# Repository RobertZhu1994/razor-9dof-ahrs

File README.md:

Razor AHRS v1.4.2
---

This is a "fab-able" version of the <a href="https://www.sparkfun.com/products/retired/10736">Sparkfun 9DOF IMU board</a>, modified so that it can be made with a desktop CNC router.

Full documentation on <a href="https://www.instructables.com/id/9-Degrees-of-Freedom-IMU/">Instructables</a>.

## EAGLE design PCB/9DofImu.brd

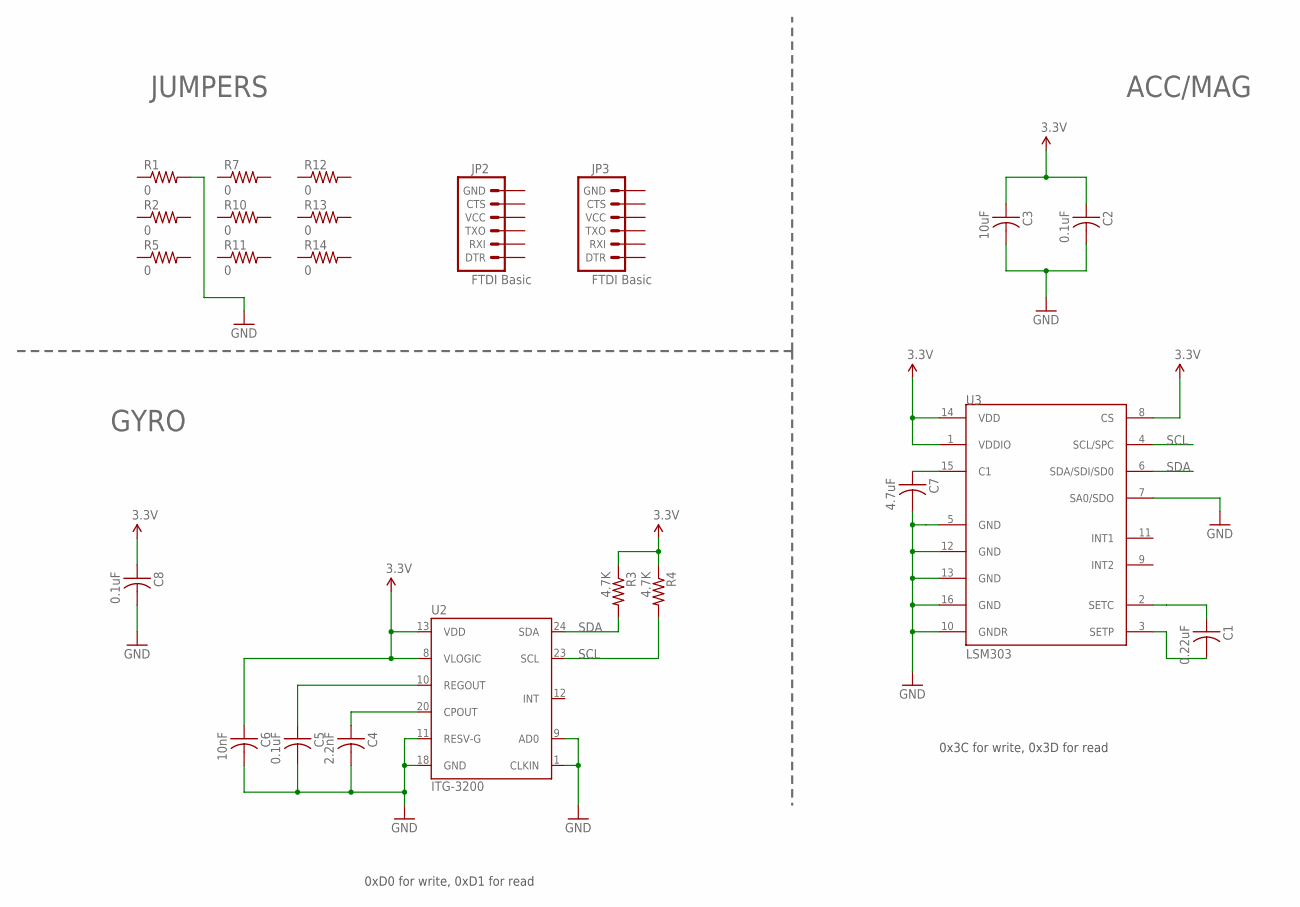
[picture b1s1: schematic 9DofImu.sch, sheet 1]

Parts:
C1: 0.22uF; C1206
C2, C5, C8: 0.1uF; C1206
C3: 10uF; C1206
C4: 2.2nF; C1206
C6: 10nF; C1206
C7: 4.7uF; C1206
JP2, JP3: FTDI Basic; 1X06-KIT
R1, R2, R5, R7, R10, R11, R12, R13, R14: 0; R1206FAB
R3: 4.7K; R1206
R4: 4.7K; R1206FAB
U2: ITG-3200; QFN-24
U3: LSM303; LGA16-3MM

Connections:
3.3V: C2.1, C3.1, C6.1, C8.1, R3.1, R4.1, U2.8 (VLOGIC), U2.13 (VDD), U3.1 (VDDIO), U3.8 (CS), U3.14 (VDD); also elsewhere on the board
GND: C2.2, C3.2, C4.2, C5.2, C6.2, C7.2, C8.2, R1.2, U2.1 (CLKIN), U2.9 (AD0), U2.11 (RESV-G), U2.18 (GND), U3.5 (GND), U3.7 (SA0/SDO), U3.10 (GNDR), U3.12 (GND), U3.13 (GND), U3.16 (GND); also elsewhere on the board
unnamed: C4.1, U2.20 (CPOUT)
unnamed: C5.1, U2.10 (REGOUT)
unnamed: C7.1, U3.15 (C1)
unnamed: C1.1, U3.2 (SETC)
unnamed: C1.2, U3.3 (SETP)
SCL: R4.2, U2.23 (SCL), U3.4 (SCL/SPC); also elsewhere on the board
SDA: R3.2, U2.24 (SDA), U3.6 (SDA/SDI/SD0); also elsewhere on the board

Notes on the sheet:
0xD0 for write, 0xD1 for read
0x3C for write, 0x3D for read
JUMPERS
ACC/MAG
GYRO

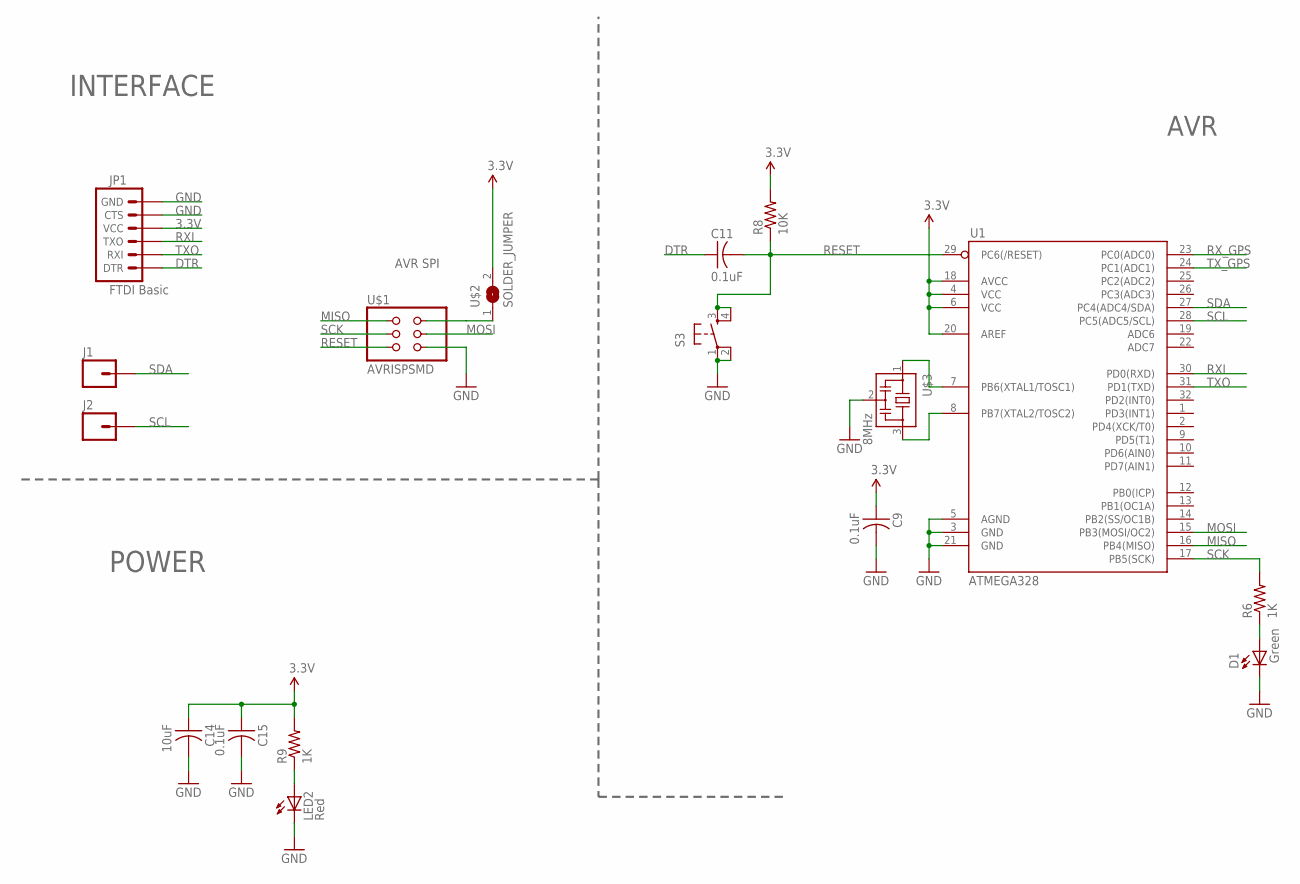
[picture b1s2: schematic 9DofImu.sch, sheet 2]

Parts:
C9, C11, C15: 0.1uF; C1206
C14: 10uF; C1206
D1: Green; LED-1206
J1, J2: M01PTH; 1X01
JP1: FTDI Basic; 1X06-KIT
LED2: Red; LED-1206
R6: 1K; R1206
R8: 10K; R1206
R9: 1K; R1206FAB
S3: 6MM_SWITCH6MM_SWITCH; 6MM_SWITCH
U1: ATMEGA328; TQFP32-08
U$1: AVRISPSMD; 2X03SMD
U$2: SOLDER_JUMPER; SJFAB
U$3: 8MHz; EFOBM

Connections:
3.3V: C9.1, C14.1, C15.1, JP1.4 (VCC), R8.2, R9.2, U1.4 (VCC), U1.6 (VCC), U1.18 (AVCC), U1.20 (AREF), U$2.2; also elsewhere on the board
DTR: C11.1, JP1.1 (DTR)
GND: C9.2, C14.2, C15.2, D1.C, JP1.5 (CTS), JP1.6 (GND), LED2.C, S3.1, S3.2 (P1), U1.3 (GND), U1.5 (AGND), U1.21 (GND), U$1.6 (GND), U$3.2; also elsewhere on the board
MISO: U1.16 (PB4(MISO)), U$1.1 (MISO)
MOSI: U1.15 (PB3(MOSI/OC2)), U$1.4 (MOSI)
unnamed: LED2.A, R9.1
unnamed: U$1.2 (VCC), U$2.1
unnamed: D1.A, R6.1
unnamed: U1.8 (PB7(XTAL2/TOSC2)), U$3.3
unnamed: U1.7 (PB6(XTAL1/TOSC1)), U$3.1
RESET: C11.2, R8.1, S3.3 (S), S3.4 (S1), U1.29 (PC6(/RESET)), U$1.5 (RST)
RXI: JP1.3 (TXO), U1.30 (PD0(RXD))
RX_GPS: U1.23 (PC0(ADC0))
SCK: R6.2, U1.17 (PB5(SCK)), U$1.3 (SCK)
SCL: J2.1, U1.28 (PC5(ADC5/SCL)); also elsewhere on the board
SDA: J1.1, U1.27 (PC4(ADC4/SDA)); also elsewhere on the board
TXO: JP1.2 (RXI), U1.31 (PD1(TXD))
TX_GPS: U1.24 (PC1(ADC1))

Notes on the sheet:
AVR
INTERFACE
POWER
AVR SPI

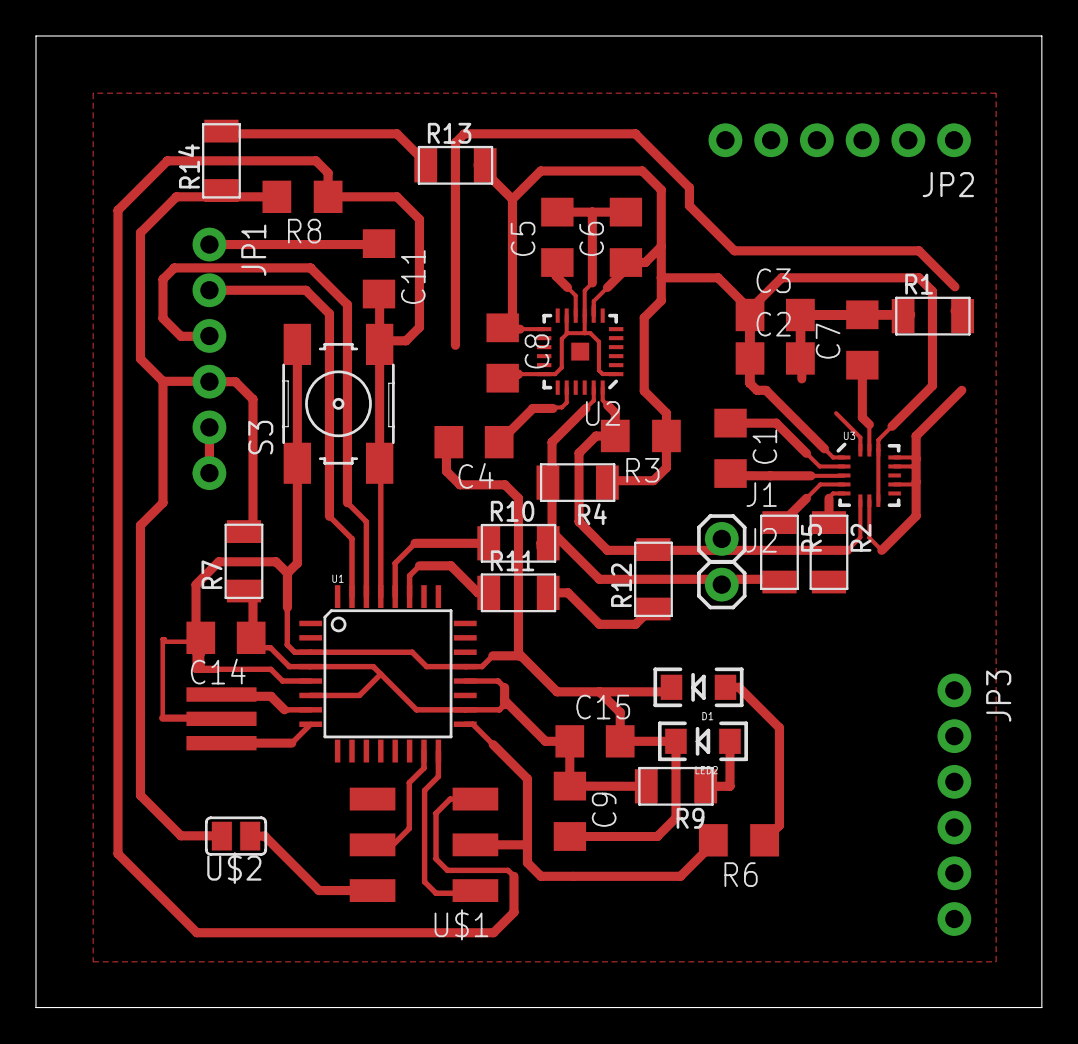
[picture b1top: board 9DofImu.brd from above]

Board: 2 copper layers, 55.9 x 54.0 mm, 40 parts (0 on the bottom side), 21 nets.

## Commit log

2014-11-12 lsm303 compatibility
2014-11-12 sign change
2014-11-13 more sign changes
2014-11-24 seems to be working now
2014-11-30 upadted pcb
2016-05-26 components diagram
2016-05-28 pcb updates
2016-05-28 small changes
2016-05-29 i2c pin headers
2016-05-29 boudary fix

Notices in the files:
parts and their libraries:
SparkFun-Connectors: Licensing: Creative Commons ShareAlike 4.0 International - https://creativecommons.org/licenses/by-sa/4.0
